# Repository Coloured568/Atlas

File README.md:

# Atlas
A homebrew MP3 player for hackclub!

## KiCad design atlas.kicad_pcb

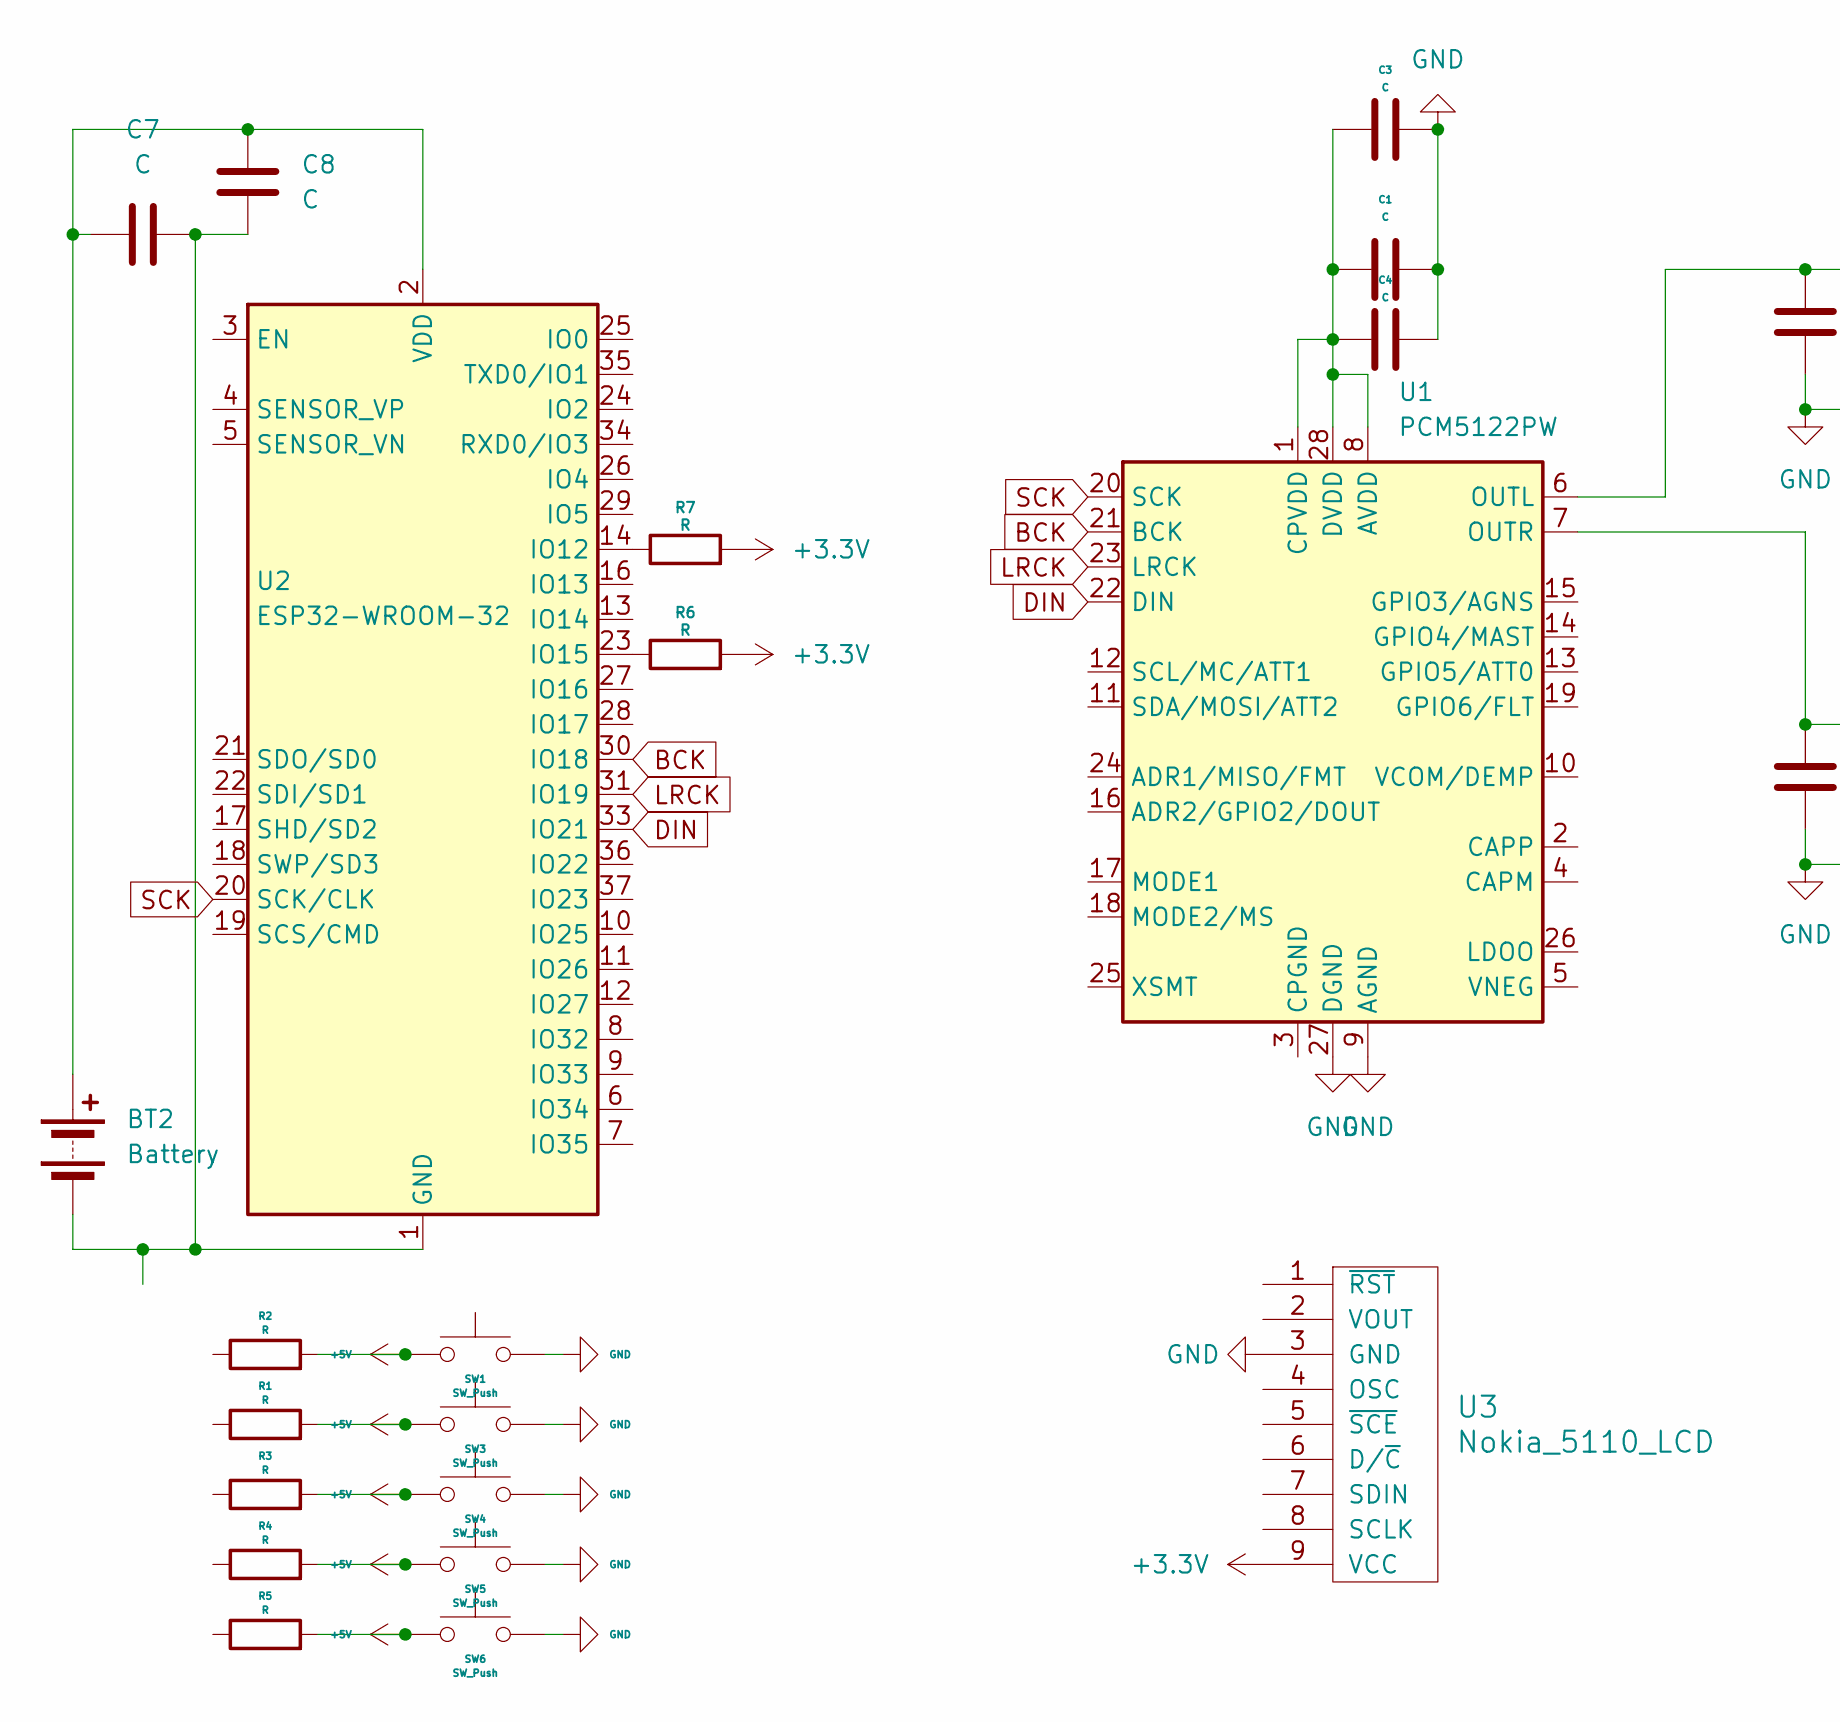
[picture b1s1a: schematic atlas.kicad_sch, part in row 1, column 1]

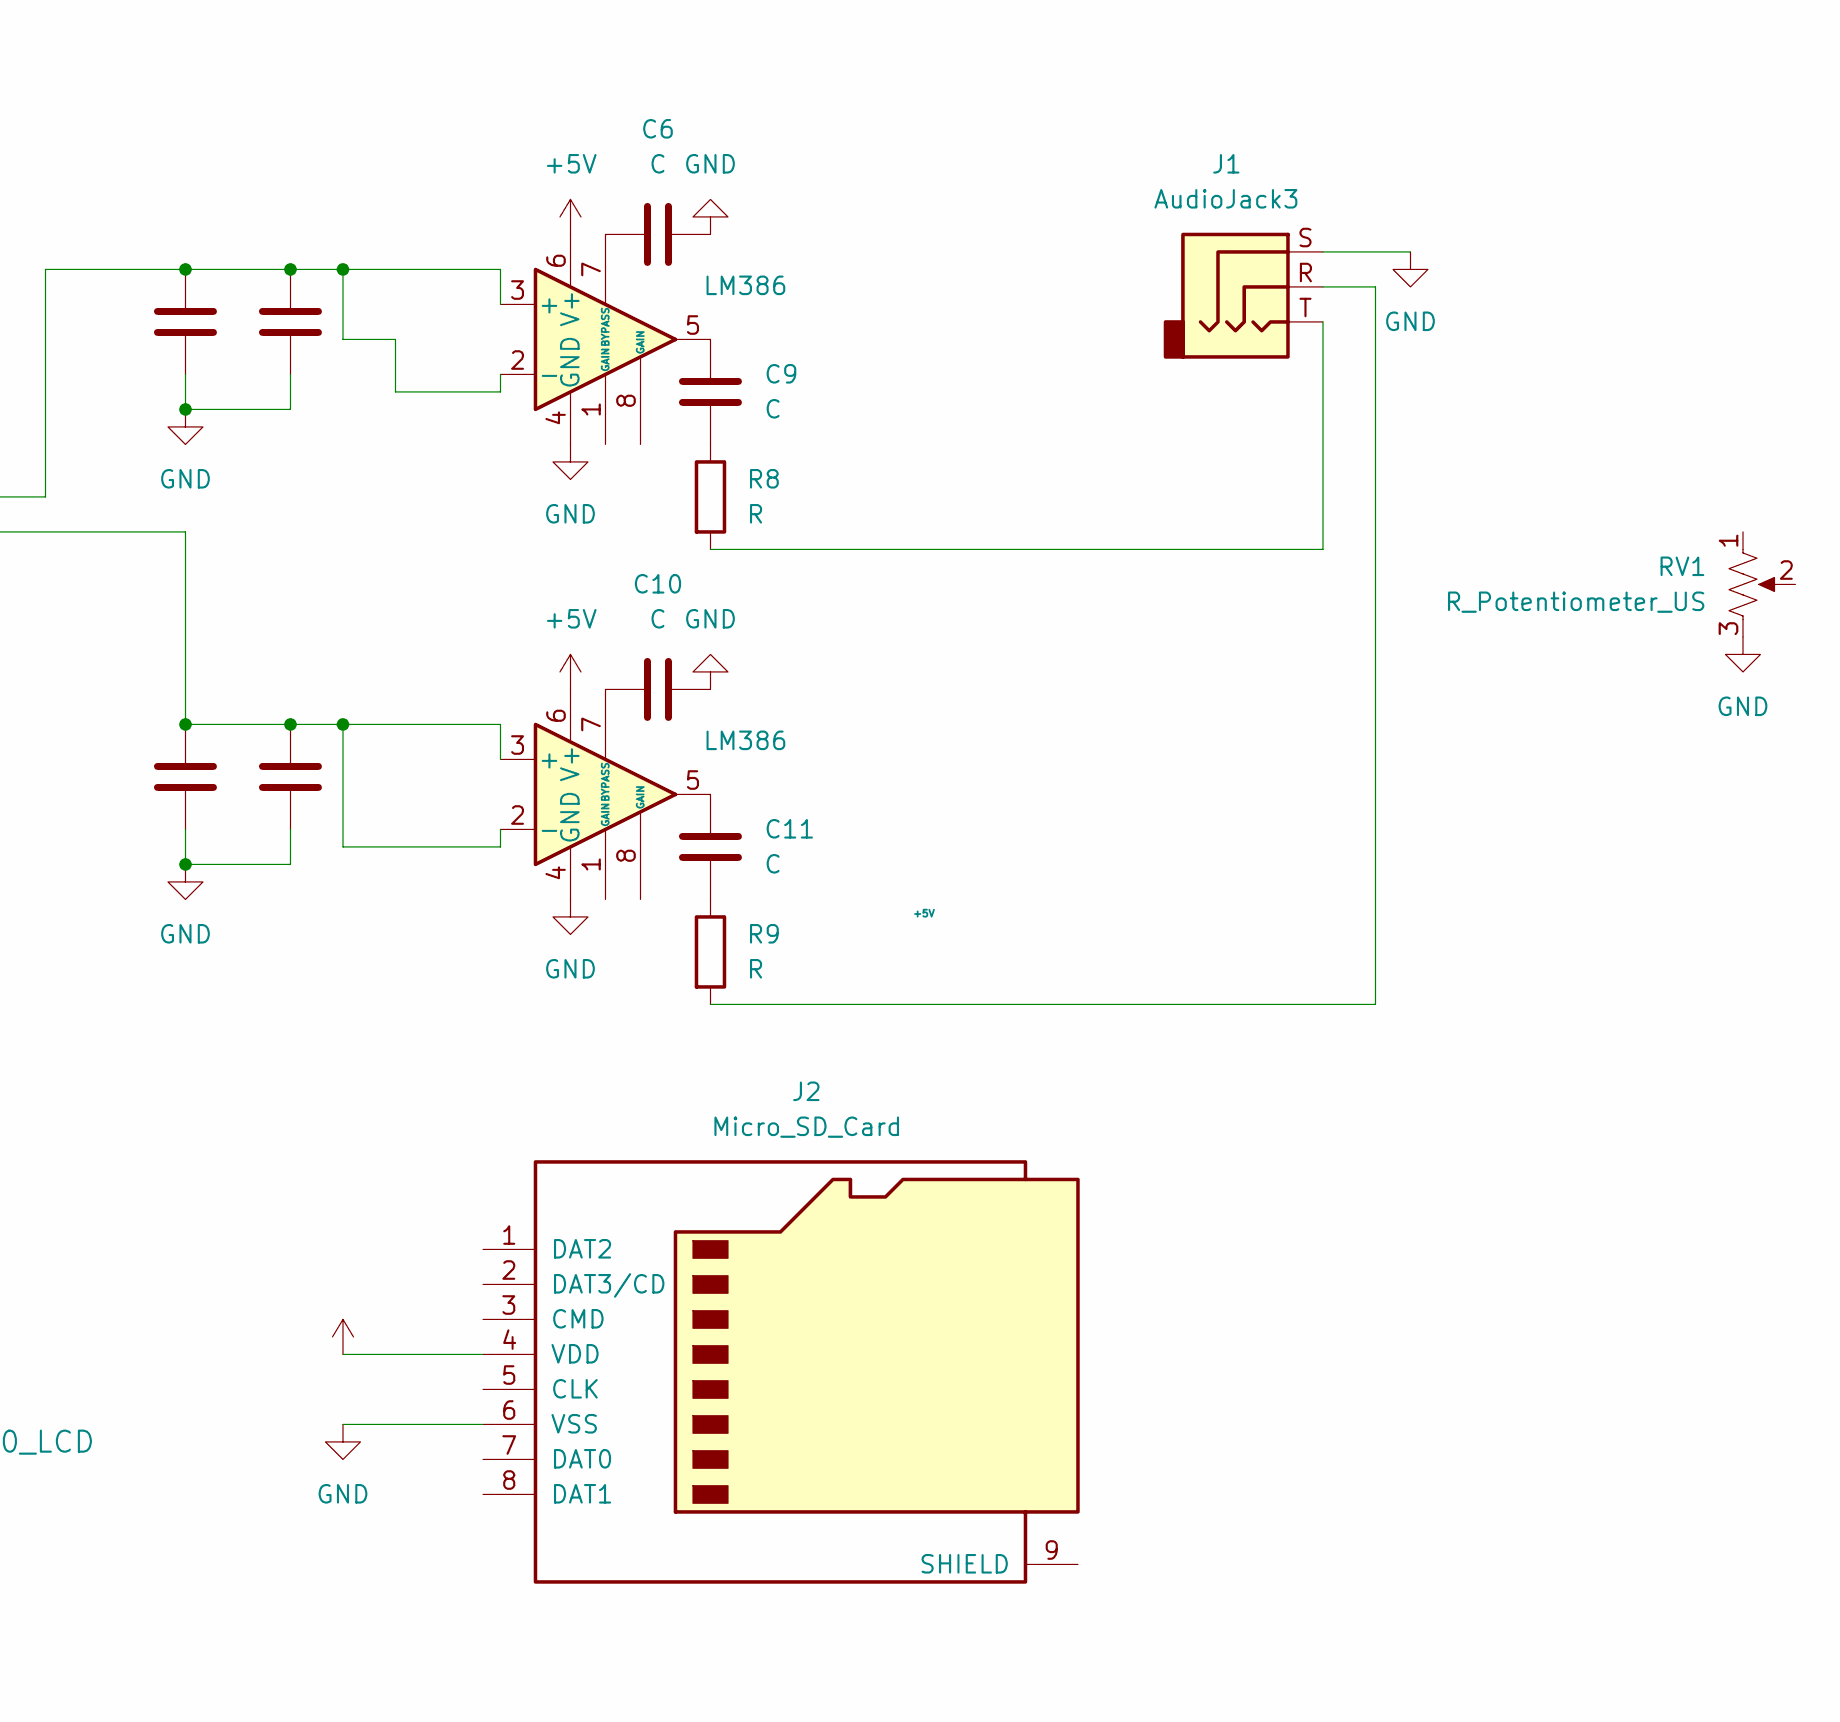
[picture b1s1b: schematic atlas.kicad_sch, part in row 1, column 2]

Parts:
BT2: Battery
C1, C2, C3, C4, C5, C6, C7, C8, C9, C10, C11, C12, C13: C; C_1808_4520Metric_Pad1.72x2.30mm_HandSolder
J1: AudioJack3; Jack_3.5mm_CUI_SJ-3523-SMT_Horizontal
J2: Micro_SD_Card; microSD_HC_Hirose_DM3AT-SF-PEJM5
R1, R2, R3, R4, R5, R6, R7, R8, R9: R; R_0201_0603Metric
RV1: R_Potentiometer_US; Potentiometer_ACP_CA14V-15_Vertical
SW1, SW3, SW4, SW5, SW6: SW_Push; SW_PUSH_6mm
U1: PCM5122PW; TSSOP-28_4.4x9.7mm_P0.65mm
U2: ESP32-WROOM-32
U3: Nokia_5110_LCD; Nokia_5110-3310_LCD
U4, U6: LM386; DIP-8_W7.62mm

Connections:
+3.3V: R6.2, R7.2, U3.9 (VCC)
+5V: J2.4 (VDD), R1.2, R2.2, R3.2, R4.2, R5.2, SW1.1, SW3.1, SW4.1, SW5.1, SW6.1, U4.6 (V+), U6.6 (V+)
BCK: U1.21 (BCK), U2.30 (IO18)
DIN: U1.22 (DIN), U2.33 (IO21)
GND: C1.2, C2.2, C3.2, C4.2, C5.2, C6.2, C10.2, C12.2, C13.2, J1.S, J2.6 (VSS), RV1.3, SW1.2, SW3.2, SW4.2, SW5.2, SW6.2, U1.9 (AGND), U1.27 (DGND), U3.3 (GND), U4.4 (GND), U6.4 (GND)
LRCK: U1.23 (LRCK), U2.31 (IO19)
unnamed: BT2.1 (+), C7.1, C8.1, U2.2 (VDD)
unnamed: BT2.2 (-), C7.2, C8.2, U2.1 (GND), U2.15 (GND), U2.38 (GND), U2.39 (GND)
unnamed: C9.1, U6.5
unnamed: C9.2, R8.1
unnamed: C11.1, U4.5
unnamed: C11.2, R9.1
unnamed: J1.R, R9.2
unnamed: J1.T, R8.2
unnamed: C1.1, C3.1, C4.1, U1.1 (CPVDD), U1.8 (AVDD), U1.28 (DVDD)
unnamed: C2.1, C5.1, U1.6 (OUTL), U6.2 (-), U6.3 (+)
unnamed: C12.1, C13.1, U1.7 (OUTR), U4.2 (-), U4.3 (+)
unnamed: R7.1, U2.14 (IO12)
unnamed: R6.1, U2.23 (IO15)
unnamed: C10.1, U4.7 (BYPASS)
unnamed: C6.1, U6.7 (BYPASS)
SCK: U1.20 (SCK), U2.20 (SCK/CLK)

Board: 2 copper layers, 35 parts (27 on the bottom side), 22 nets, no tracks yet.

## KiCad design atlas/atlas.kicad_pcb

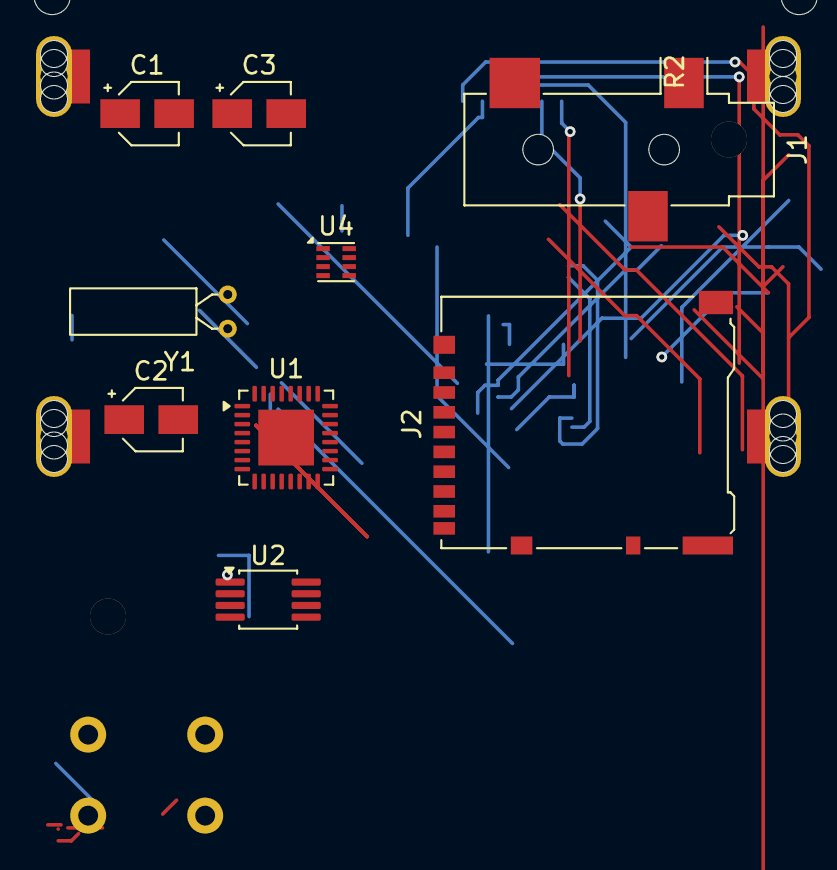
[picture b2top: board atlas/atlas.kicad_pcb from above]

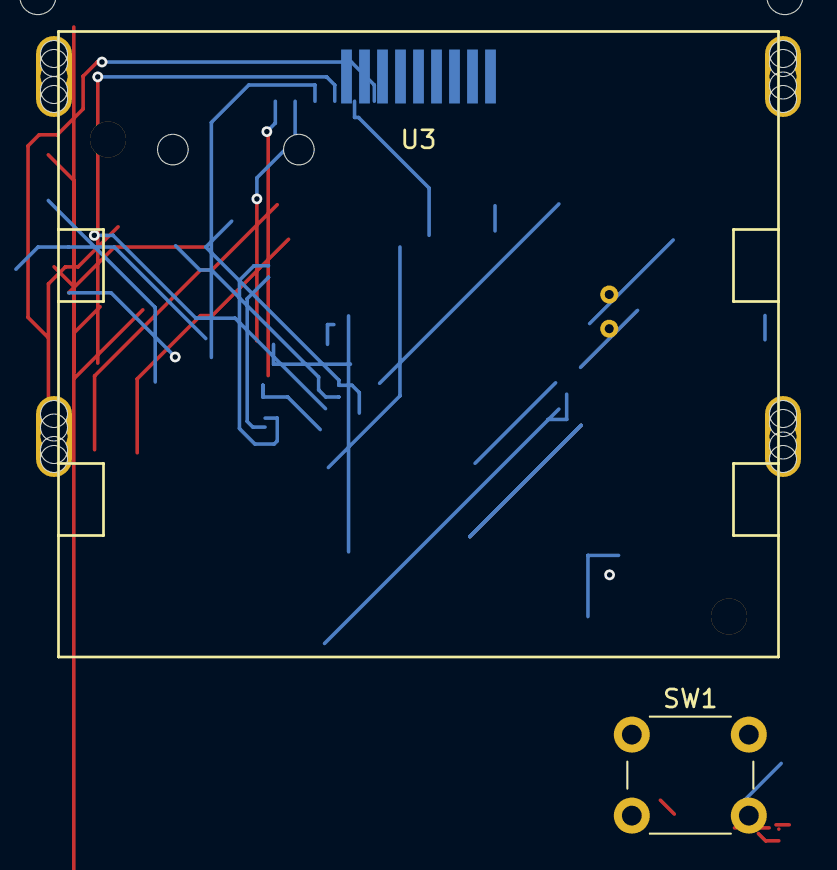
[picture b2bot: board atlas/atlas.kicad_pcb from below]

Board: 2 copper layers, 12 parts (2 on the bottom side), 18 nets.

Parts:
C1, C2, C3: C; CP_Elec_3x5.3
J1: AudioJack3; Jack_3.5mm_CUI_SJ-3523-SMT_Horizontal
J2: Micro_SD_Card; microSD_HC_Hirose_DM3AT-SF-PEJM5
R2: R; R_0201_0603Metric
SW1: SW_Push; SW_PUSH_6mm
U1: ATmega328-P; HVQFN-32-1EP_5x5mm_P0.5mm_EP3.1x3.1mm
U2: DAC8571IDGK; MSOP-8_3x3mm_P0.65mm
U3: Nokia_5110_LCD; Nokia_5110-3310_LCD
U4: NE5532; LFCSP-8_2x2mm_P0.5mm
Y1: Crystal; Crystal_C26-LF_D2.1mm_L6.5mm_Horizontal

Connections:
+5V: J2.4 (VDD), R2.1, SW1.2, U2.1 (V_{DD}), U2.2 (V_{REF})
GND: C1.2, C3.2, J2.6 (VSS), SW1.1, U2.5 (A0), U2.8 (GND), U3.3 (GND)
unnamed: U1.8 (GND), U1.22 (GND)
unnamed: C1.1, Y1.2
unnamed: C2.1, J1.R, J1.T
unnamed: C2.2, J1.S
unnamed: U1.7 (VCC), U1.20 (AVCC), U1.21 (AREF)
unnamed: U1.9 (XTAL1/PB6), Y1.1
unnamed: C3.1, U1.10 (XTAL2/PB7)
unnamed: R2.2, U1.1 (~RESET/PC6)
unnamed: U2.4 (V_{OUT}), U4.3 (+)
unnamed: U2.3 (V_{SENSE}), U4.2 (-)
PD2: U1.4 (PD2), U2.6 (SCL)
PD3: U1.5 (PD3), U2.7 (SDA)
PD4: J2.3 (CMD), U1.6 (PD4)
PD5: J2.5 (CLK), U1.11 (PD5), U3.8 (SCLK)
PD6: J2.7 (DAT0), U1.12 (PD6)
PD7: J2.8 (DAT1), U1.13 (PD7)

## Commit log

2026-01-11 Delete atlas directory
    overwriting
